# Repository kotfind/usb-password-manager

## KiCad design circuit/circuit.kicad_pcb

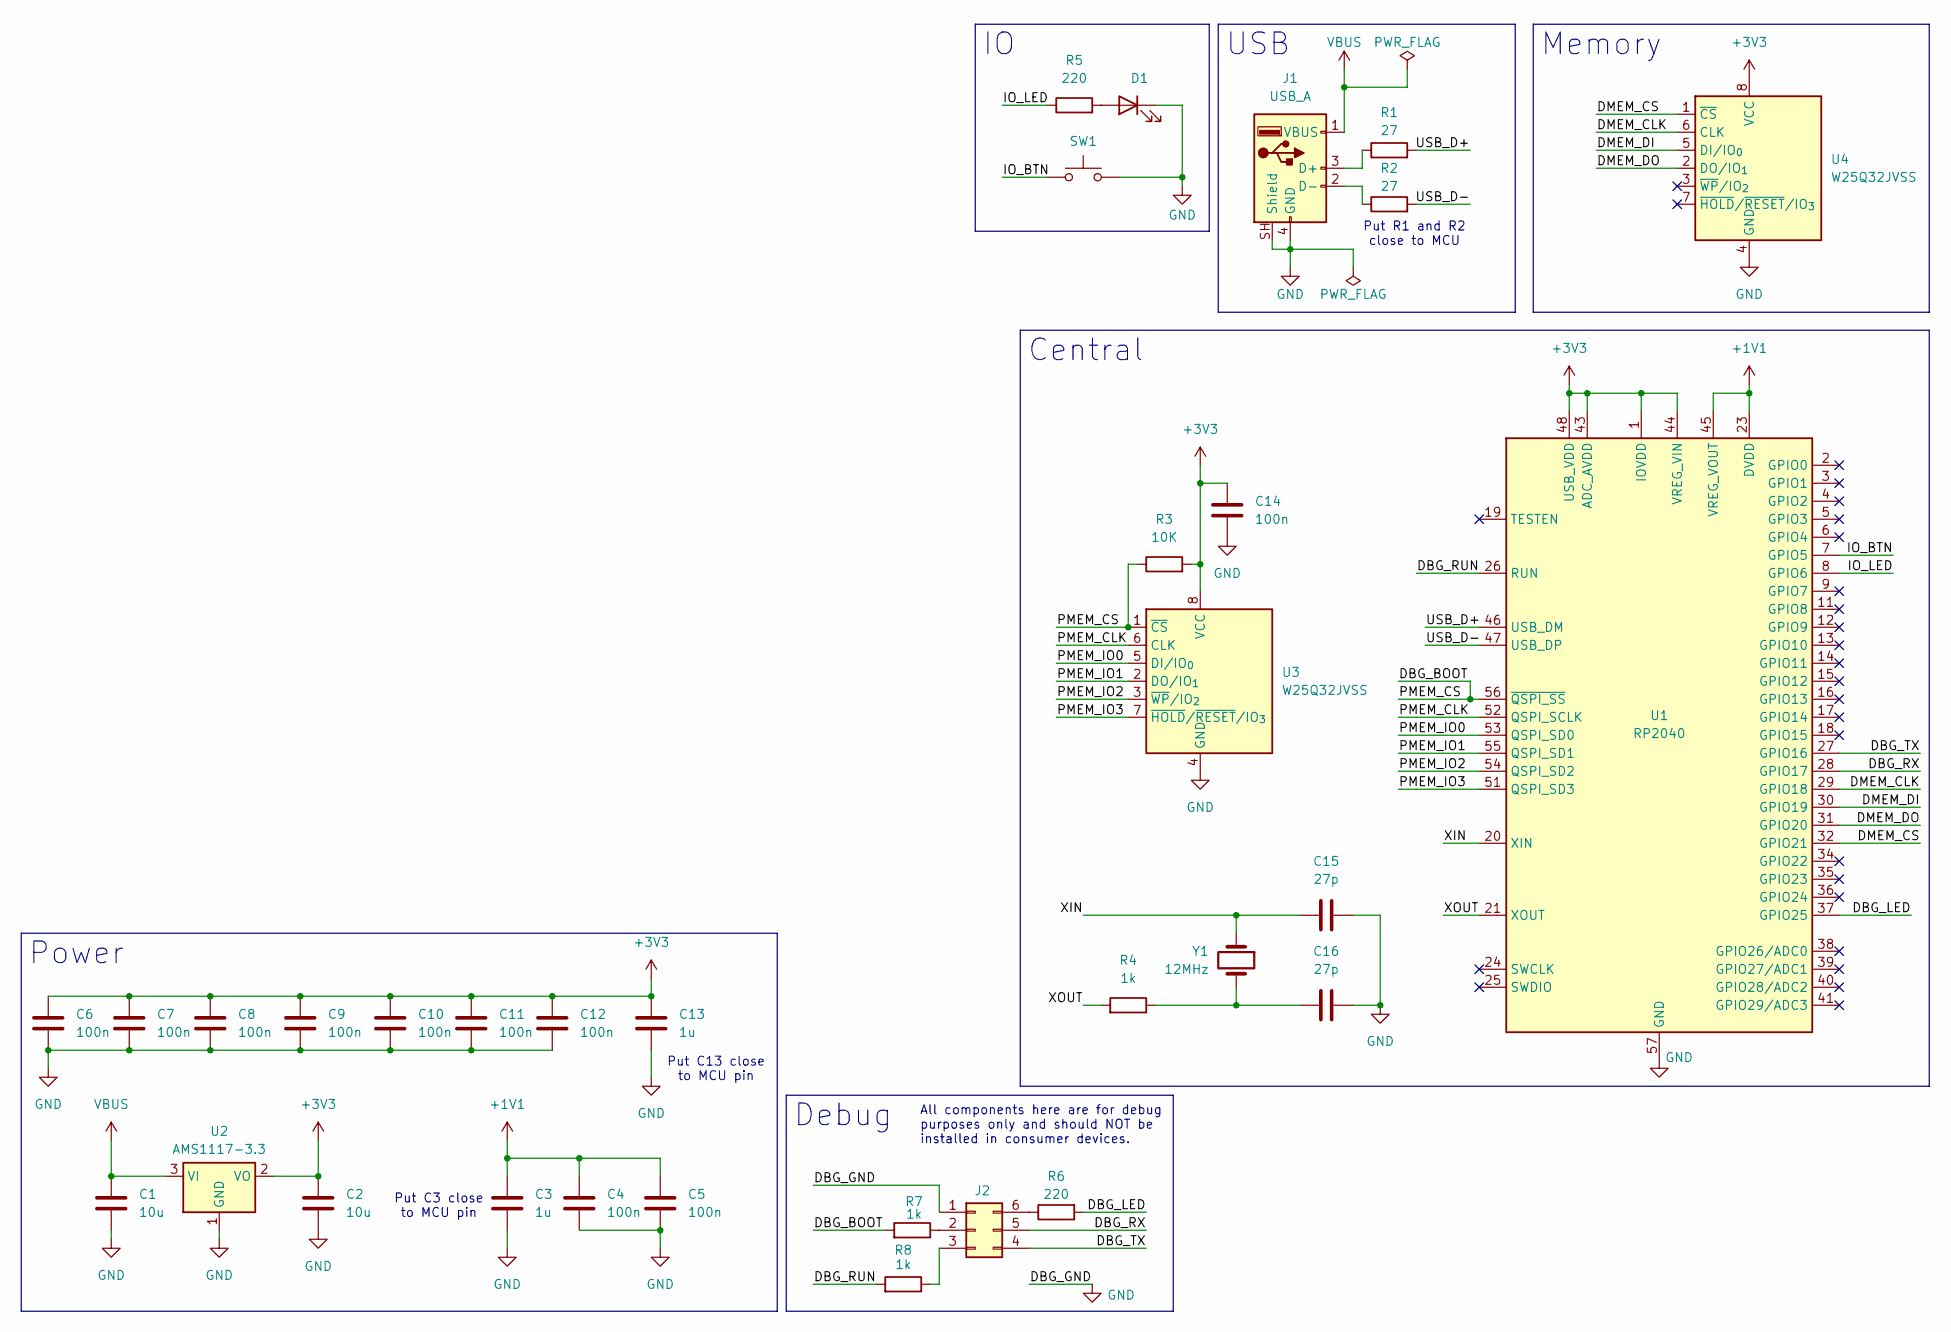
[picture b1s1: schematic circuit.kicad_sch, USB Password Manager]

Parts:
C1, C2: 10u; C_0805_2012Metric
C3, C13: 1u; C_0805_2012Metric
C4, C5, C6, C7, C8, C9, C10, C11, C12, C14: 100n; C_0805_2012Metric
C15, C16: 27p; C_0805_2012Metric
D1: LED_D5.0mm
J1: USB_A; USB_A_CNCTech_1001-011-01101_Horizontal
J2: PinSocket_2x03_P2.54mm_Horizontal
R1, R2: 27; R_0805_2012Metric
R3: 10K; R_0805_2012Metric
R4, R7, R8: 1k; R_0805_2012Metric
R5, R6: 220; R_0805_2012Metric
SW1: SW_PUSH_6mm_H5mm
U1: RP2040; QFN-56-1EP_7x7mm_P0.4mm_EP3.2x3.2mm
U2: AMS1117-3.3; SOT-223-3_TabPin2
U3, U4: W25Q32JVSS; SOIC-8_5.3x5.3mm_P1.27mm
Y1: 12MHz; Crystal_SMD_SeikoEpson_FA238-4Pin_3.2x2.5mm

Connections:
+1V1: C3.1, C4.1, C5.1, U1.23 (DVDD), U1.45 (VREG_VOUT), U1.50 (DVDD)
+3V3: C2.1, C6.1, C7.1, C8.1, C9.1, C10.1, C11.1, C12.1, C13.1, C14.1, R3.2, U1.1 (IOVDD), U1.10 (IOVDD), U1.22 (IOVDD), U1.33 (IOVDD), U1.42 (IOVDD), U1.43 (ADC_AVDD), U1.44 (VREG_VIN), U1.48 (USB_VDD), U1.49 (IOVDD), U2.2 (VO), U3.8 (VCC), U4.8 (VCC)
/DBG_BOOT: R3.1, R7.2, U1.56 (~QSPI_SS), U3.1 (~CS)
/DBG_LED: R6.2, U1.37 (GPIO25)
/DBG_RUN: R8.2, U1.26 (RUN)
/DBG_RX: J2.5, U1.28 (GPIO17)
/DBG_TX: J2.4, U1.27 (GPIO16)
/DMEM_CLK: U1.29 (GPIO18), U4.6 (CLK)
/DMEM_CS: U1.32 (GPIO21), U4.1 (~CS)
/DMEM_DI: U1.30 (GPIO19), U4.5 (DI/IO_{0})
/DMEM_DO: U1.31 (GPIO20), U4.2 (DO/IO_{1})
/IO_BTN: SW1.1, U1.7 (GPIO5)
/IO_LED: R5.1, U1.8 (GPIO6)
/PMEM_CLK: U1.52 (QSPI_SCLK), U3.6 (CLK)
/PMEM_IO0: U1.53 (QSPI_SD0), U3.5 (DI/IO_{0})
/PMEM_IO1: U1.55 (QSPI_SD1), U3.2 (DO/IO_{1})
/PMEM_IO2: U1.54 (QSPI_SD2), U3.3 (~WP/IO_{2})
/PMEM_IO3: U1.51 (QSPI_SD3), U3.7 (~HOLD/~RESET/IO_{3})
/USB_D+: R1.2, U1.46 (USB_DM)
/USB_D-: R2.2, U1.47 (USB_DP)
/XIN: C15.2, U1.20 (XIN), Y1.1
/XOUT: R4.2, U1.21 (XOUT)
GND: C1.2, C2.2, C3.2, C4.2, C5.2, C6.2, C7.2, C8.2, C9.2, C10.2, C11.2, C12.2, C13.2, C14.2, C15.1, C16.1, D1.1 (K), J1.4 (GND), J1.SH (Shield), J2.1, SW1.2, U1.57 (GND), U2.1 (GND), U3.4 (GND), U4.4 (GND)
unnamed: C16.2, R4.1, Y1.2
unnamed: D1.2 (A), R5.2
unnamed: J1.3 (D+), R1.1
unnamed: J1.2 (D-), R2.1
unnamed: J2.2, R7.1
unnamed: J2.3, R8.1
unnamed: J2.6, R6.1
VBUS: C1.1, J1.1 (VBUS), U2.3 (VI)

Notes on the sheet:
All components here are for debug purposes only and should NOT be installed in consumer devices.
Put C3 close to MCU pin
Put C13 close to MCU pin
Put R1 and R2 close to MCU
Debug
Power
Central
Memory
USB

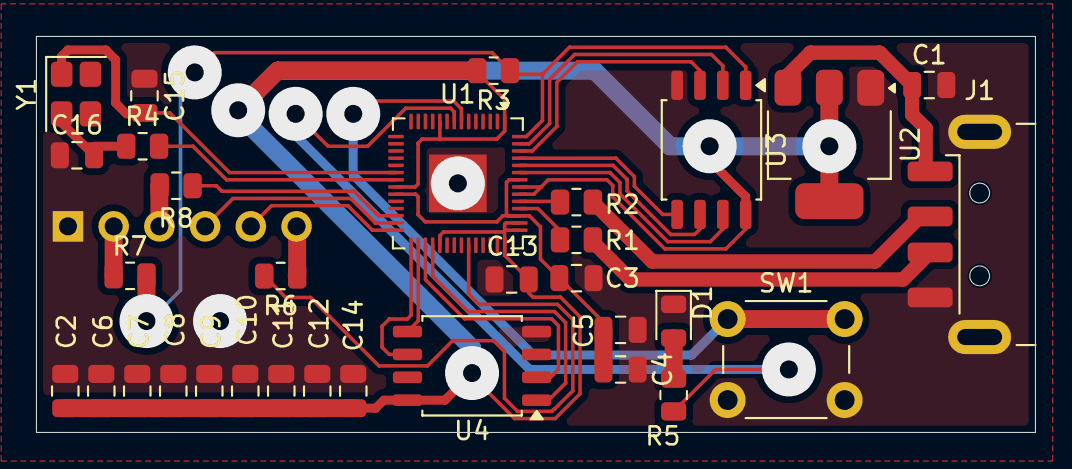
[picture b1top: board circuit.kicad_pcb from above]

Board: 2 copper layers, 55.5 x 22.0 mm, 33 parts (1 on the bottom side), 31 nets.

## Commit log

2026-05-21 Fix ERC errors
2026-05-21 specify components
2026-05-22 PCB v1
2026-05-22 PCB v2
2026-05-22 finalize PCB
2026-05-22 Final PCB fixes
2026-05-22 add images
